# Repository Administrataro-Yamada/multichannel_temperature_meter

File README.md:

# multichannel_temperature_meter

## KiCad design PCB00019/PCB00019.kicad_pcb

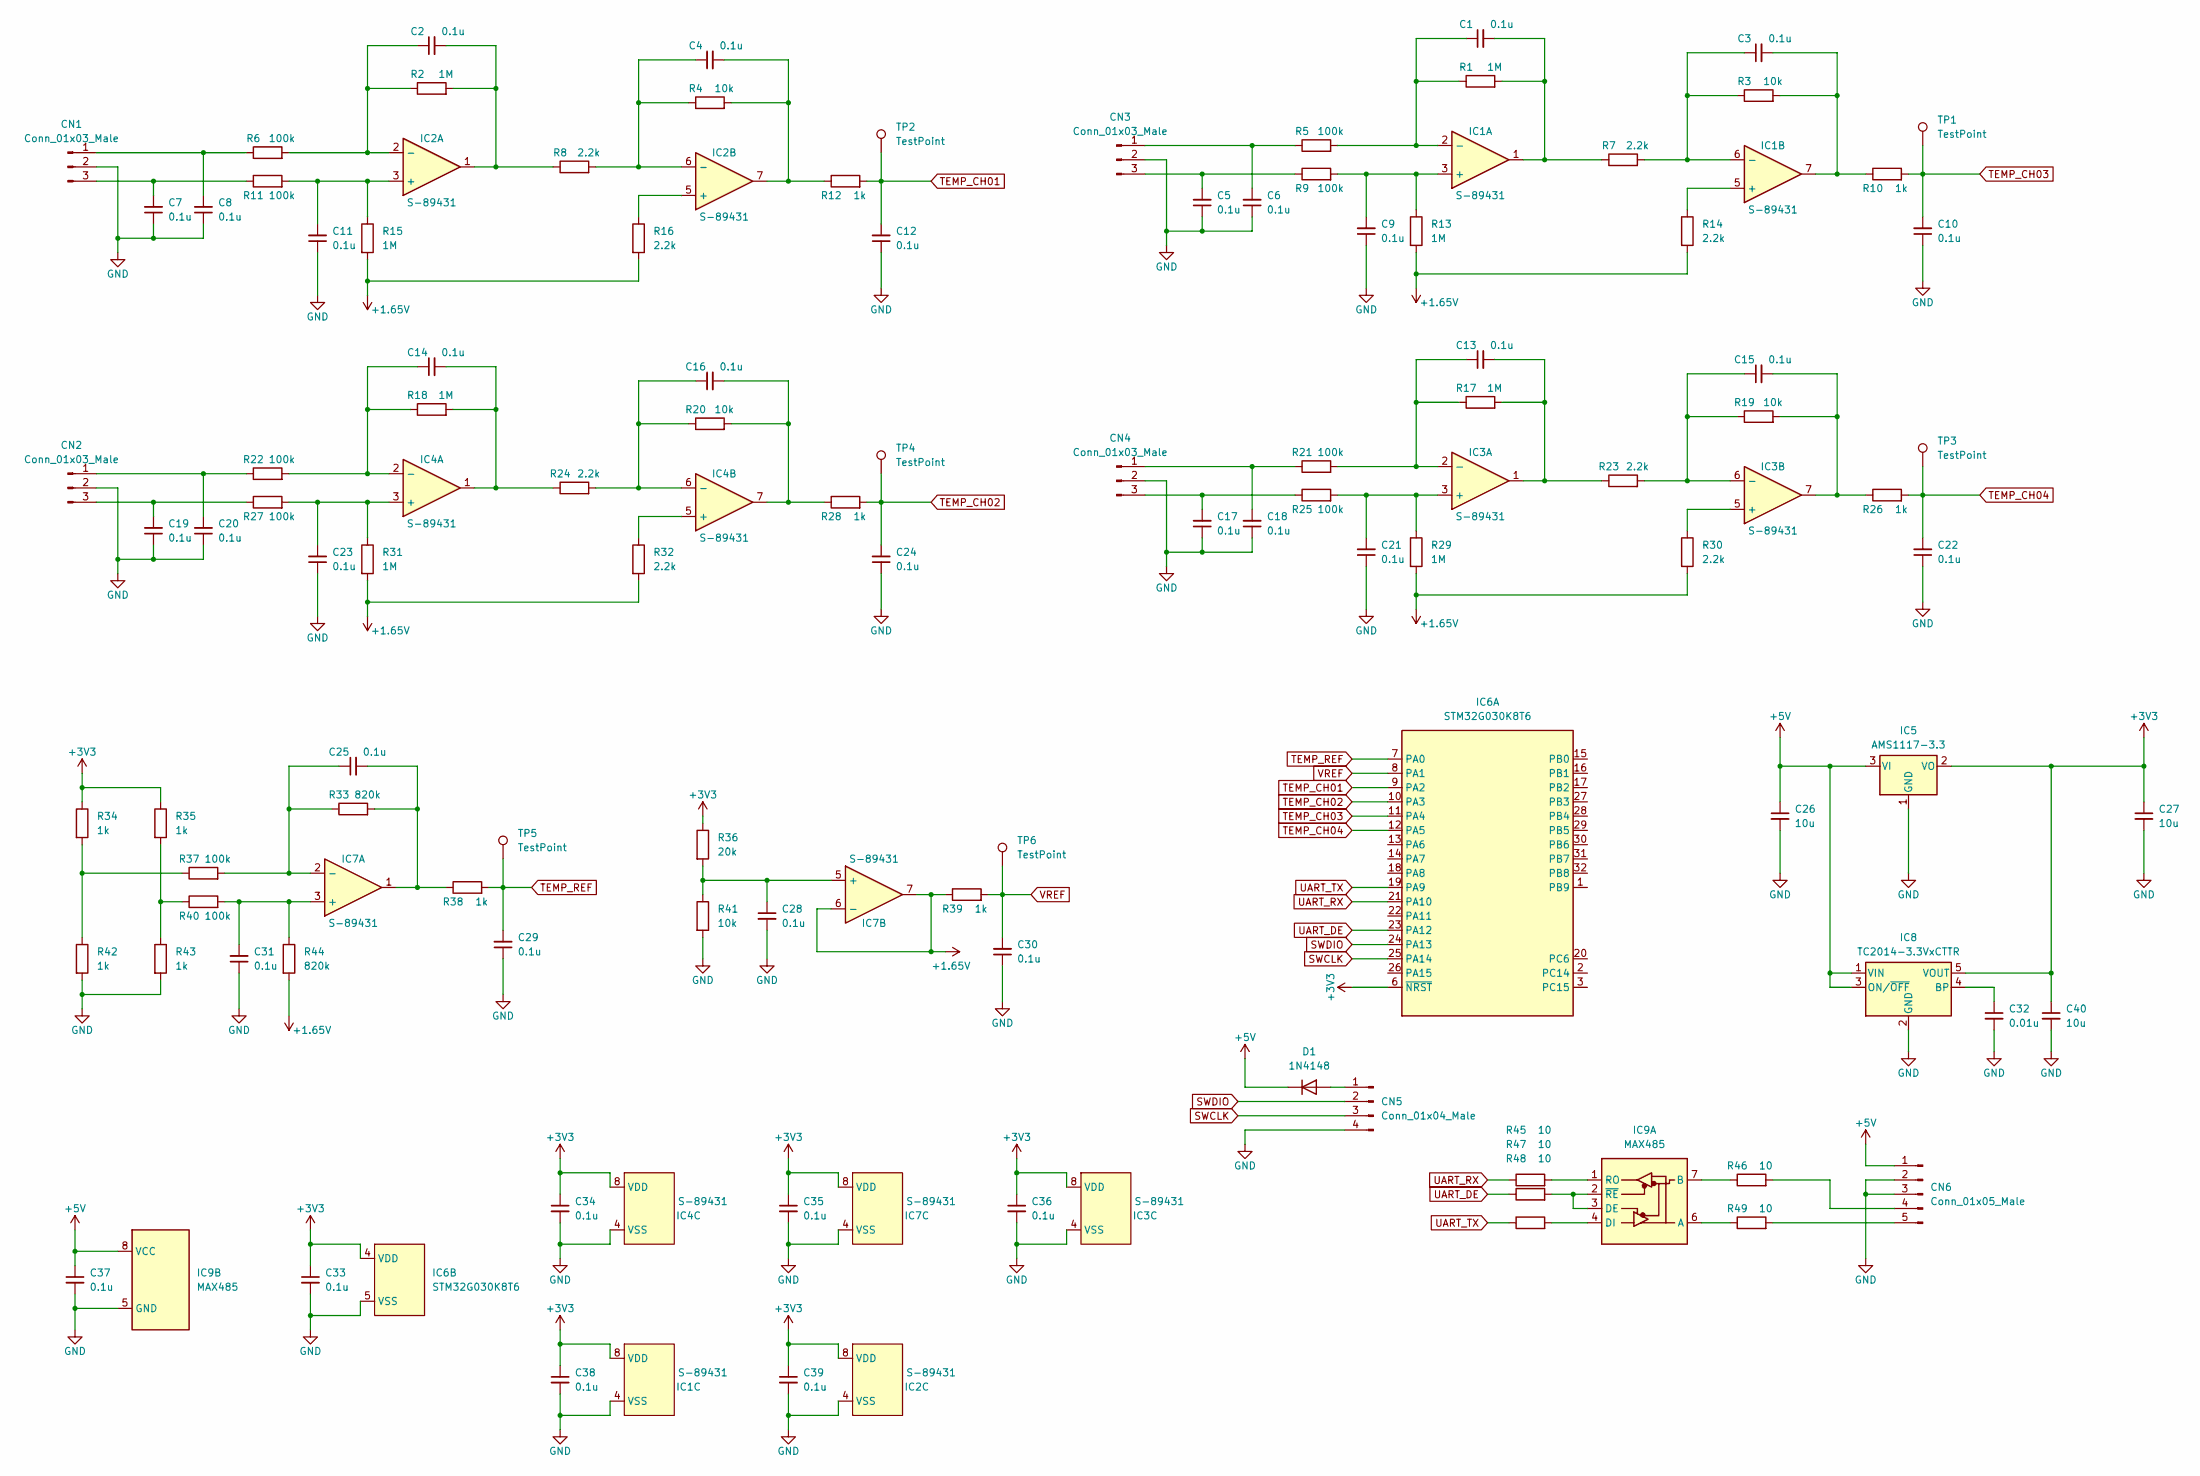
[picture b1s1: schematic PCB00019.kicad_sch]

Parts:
C1, C2, C3, C4, C5, C6, C7, C8, C9, C10, C11, C12, C13, C14, C15, C16, C17, C18, C19, C20, C21, C22, C23, C24, C25, C28, C29, C30, C31, C33, C34, C35, C36, C37, C38, C39: 0.1u; C_0603_1608Metric
C26, C27, C40: 10u; C_0805_2012Metric
C32: 0.01u; C_0805_2012Metric
CN1, CN2, CN3, CN4: Conn_01x03_Male; TerminalBlock_bornier-3_P5.08mm
CN5: Conn_01x04_Male; PinHeader_1x04_P2.54mm_Vertical
CN6: Conn_01x05_Male; TerminalBlock_bornier-5_P5.08mm
D1: 1N4148; D_SOD-123
IC1, IC2, IC3, IC4, IC7: S-89431; MSOP-8_3x3mm_P0.65mm
IC5: AMS1117-3.3; SOT-223-3_TabPin2
IC6: STM32G030K8T6; LQFP-32_7x7mm_P0.8mm
IC8: TC2014-3.3VxCTTR; SOT-23-5
IC9: MAX485; SOIC-8_3.9x4.9mm_P1.27mm
R1, R2, R13, R15, R17, R18, R29, R31: 1M; R_0603_1608Metric
R3, R4, R19, R20, R41: 10k; R_0603_1608Metric
R5, R6, R9, R11, R21, R22, R25, R27, R37, R40: 100k; R_0603_1608Metric
R7, R8, R14, R16, R23, R24, R30, R32: 2.2k; R_0603_1608Metric
R10, R12, R26, R28, R34, R35, R38, R39, R42: 1k; R_0603_1608Metric
R33, R44: 820k; R_0603_1608Metric
R36: 20k; R_0603_1608Metric
R43: 1k; R_Axial_DIN0207_L6.3mm_D2.5mm_P10.16mm_Horizontal
R45, R46, R47, R48, R49: 10; R_0603_1608Metric
TP1, TP2, TP3, TP4, TP5, TP6: TestPoint; TestPoint_Pad_2.0x2.0mm

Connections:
+1V5: IC7.6 (-), IC7.7, R13.2, R14.2, R15.2, R16.2, R29.2, R30.2, R31.2, R32.2, R39.1, R44.2
+3V3: C27.1, C33.1, C34.1, C35.1, C36.1, C38.1, C39.1, C40.1, IC1.8 (VDD), IC2.8 (VDD), IC3.8 (VDD), IC4.8 (VDD), IC5.2 (VO), IC6.4 (VDD), IC6.6 (~NRST), IC7.8 (VDD), IC8.5 (VOUT), R34.1, R35.1, R36.1
+5V: C26.1, C37.1, CN6.1, D1.1 (K), IC5.3 (VI), IC8.1 (VIN), IC8.3 (ON/~OFF), IC9.8 (VCC)
GND: C5.1, C6.1, C7.1, C8.1, C9.1, C10.1, C11.1, C12.1, C17.1, C18.1, C19.1, C20.1, C21.1, C22.1, C23.1, C24.1, C26.2, C27.2, C28.2, C29.1, C30.1, C31.1, C32.2, C33.2, C34.2, C35.2, C36.2, C37.2, C38.2, C39.2, C40.2, CN1.2, CN2.2, CN3.2, CN4.2, CN5.4, CN6.2, CN6.3, IC1.4 (VSS), IC2.4 (VSS), IC3.4 (VSS), IC4.4 (VSS), IC5.1 (GND), IC6.5 (VSS), IC7.4 (VSS), IC8.2 (GND), IC9.5 (GND), R41.2, R42.2, R43.2
unnamed: C1.1, IC1.2 (-), R1.1, R5.2
unnamed: C1.2, IC1.1, R1.2, R7.1
unnamed: C2.1, IC2.2 (-), R2.1, R6.2
unnamed: C2.2, IC2.1, R2.2, R8.1
unnamed: C3.1, IC1.6 (-), R3.1, R7.2
unnamed: C3.2, IC1.7, R3.2, R10.1
unnamed: C4.1, IC2.6 (-), R4.1, R8.2
unnamed: C4.2, IC2.7, R4.2, R12.1
unnamed: C5.2, CN3.3, R9.1
unnamed: C6.2, CN3.1, R5.1
unnamed: C7.2, CN1.3, R11.1
unnamed: C8.2, CN1.1, R6.1
unnamed: C9.2, IC1.3 (+), R9.2, R13.1
unnamed: C11.2, IC2.3 (+), R11.2, R15.1
unnamed: C13.1, IC3.2 (-), R17.1, R21.2
unnamed: C13.2, IC3.1, R17.2, R23.1
unnamed: C14.1, IC4.2 (-), R18.1, R22.2
unnamed: C14.2, IC4.1, R18.2, R24.1
unnamed: C15.1, IC3.6 (-), R19.1, R23.2
unnamed: C15.2, IC3.7, R19.2, R26.1
unnamed: C16.1, IC4.6 (-), R20.1, R24.2
unnamed: C16.2, IC4.7, R20.2, R28.1
unnamed: C17.2, CN4.3, R25.1
unnamed: C18.2, CN4.1, R21.1
unnamed: C19.2, CN2.3, R27.1
unnamed: C20.2, CN2.1, R22.1
unnamed: C21.2, IC3.3 (+), R25.2, R29.1
unnamed: C23.2, IC4.3 (+), R27.2, R31.1
unnamed: C25.1, IC7.2 (-), R33.1, R37.2
unnamed: C25.2, IC7.1, R33.2, R38.1
unnamed: C28.1, IC7.5 (+), R36.2, R41.1
unnamed: C31.2, IC7.3 (+), R40.2, R44.1
unnamed: C32.1, IC8.4 (BP)
unnamed: CN6.4, R46.2
unnamed: CN6.5, R49.2
unnamed: CN5.1, D1.2 (A)
unnamed: IC1.5 (+), R14.1
unnamed: IC2.5 (+), R16.1
unnamed: IC3.5 (+), R30.1
unnamed: IC4.5 (+), R32.1
unnamed: IC9.1 (RO), R45.2
unnamed: IC9.2 (~RE), IC9.3 (DE), R47.2
unnamed: IC9.4 (DI), R48.2
unnamed: IC9.6 (A), R49.1
unnamed: IC9.7 (B), R46.1
unnamed: R34.2, R37.1, R42.1
unnamed: R35.2, R40.1, R43.1
SWCLK: CN5.3, IC6.25 (PA14)
SWDIO: CN5.2, IC6.24 (PA13)
TEMP_CH01: C12.2, IC6.9 (PA2), R12.2, TP2.1
TEMP_CH02: C24.2, IC6.10 (PA3), R28.2, TP4.1
TEMP_CH03: C10.2, IC6.11 (PA4), R10.2, TP1.1
TEMP_CH04: C22.2, IC6.12 (PA5), R26.2, TP3.1
TEMP_REF: C29.2, IC6.7 (PA0), R38.2, TP5.1
UART_DE: IC6.23 (PA12), R47.1
UART_RX: IC6.21 (PA10), R45.1
UART_TX: IC6.19 (PA9), R48.1
VREF: C30.2, IC6.8 (PA1), R39.2, TP6.1

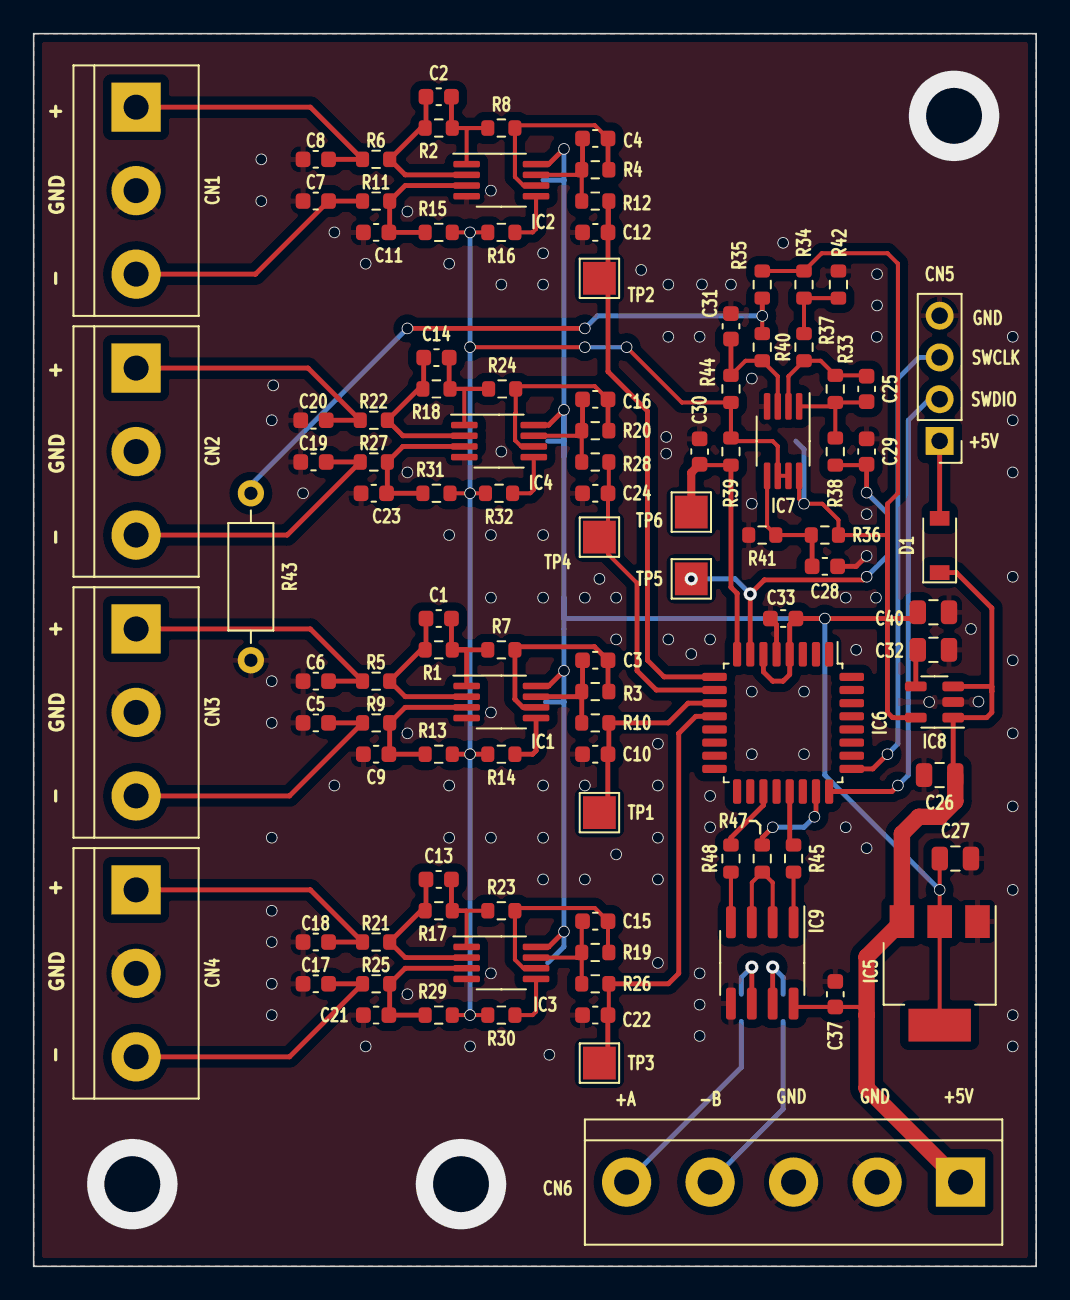
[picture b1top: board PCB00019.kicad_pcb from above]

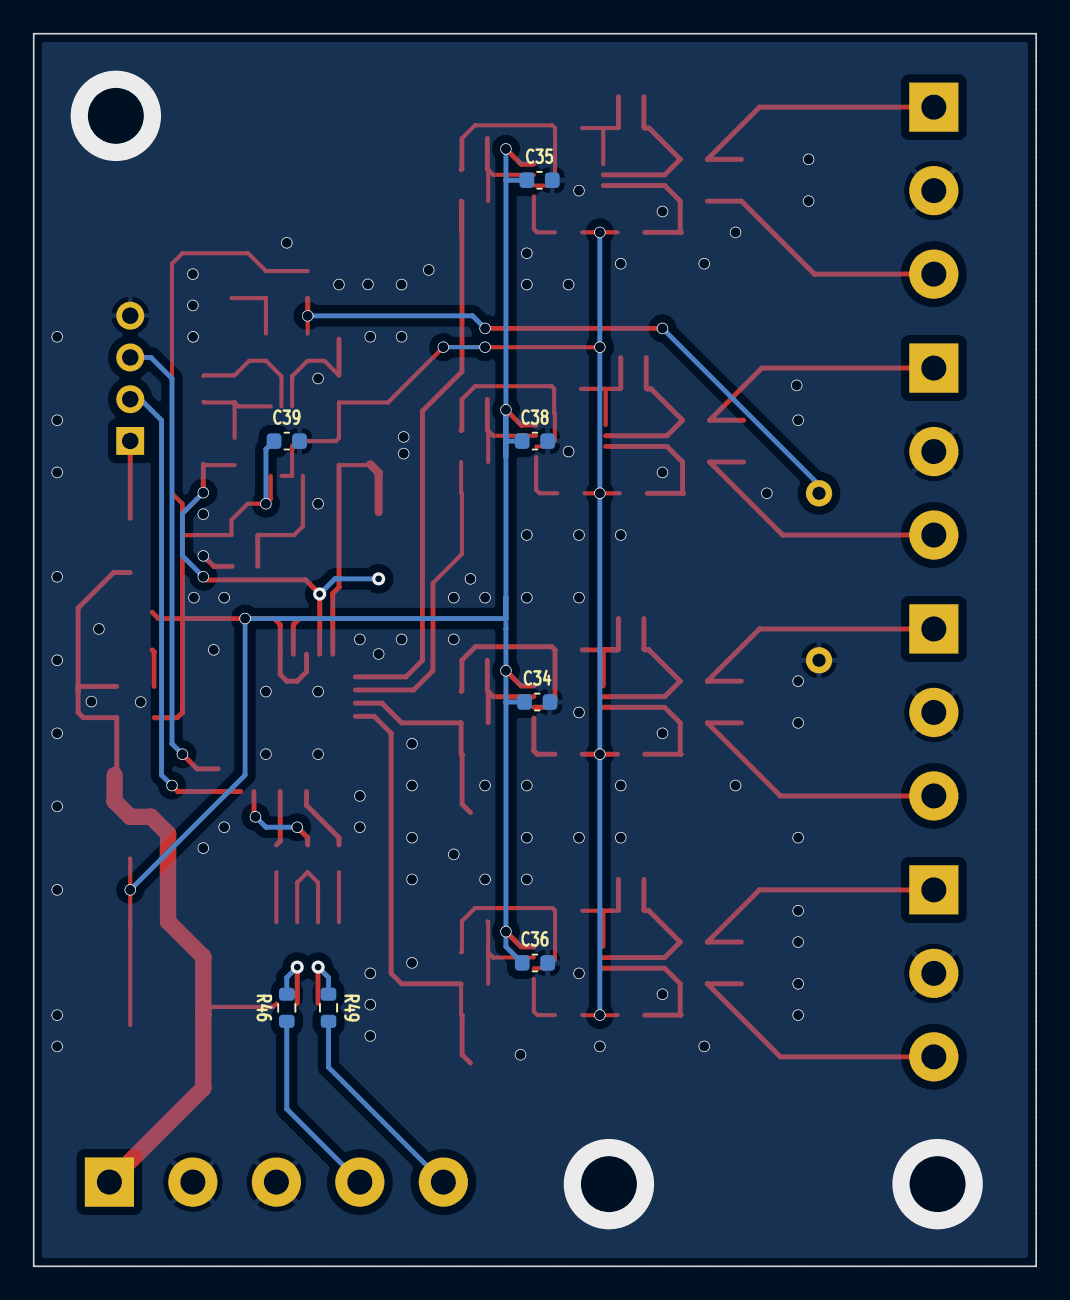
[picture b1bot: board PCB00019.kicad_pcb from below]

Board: 2 copper layers, 61.0 x 75.0 mm, 111 parts (7 on the bottom side), 62 nets.

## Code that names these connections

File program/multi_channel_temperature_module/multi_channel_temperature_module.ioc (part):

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Mcu.Name=STM32G030K(6-8)Tx
Mcu.Package=LQFP32
Mcu.UserName=STM32G030K8Tx
PA0.Mode=IN0
PA0.Signal=ADC1_IN0
PA1.Mode=IN1
PA1.Signal=ADC1_IN1
PA10.Mode=Asynchronous
PA10.Signal=USART1_RX
PA12\ [PA10].Mode=Hardware Flow Control (RS485)
PA12\ [PA10].Signal=USART1_DE
PA13.Mode=Serial_Wire
PA13.Signal=SYS_SWDIO
PA14-BOOT0.Mode=Serial_Wire
PA14-BOOT0.Signal=SYS_SWCLK
PA2.Mode=IN2
PA2.Signal=ADC1_IN2
PA3.Mode=IN3
PA3.Signal=ADC1_IN3
PA4.Mode=IN4
PA4.Signal=ADC1_IN4
PA5.Mode=IN5
PA5.Signal=ADC1_IN5
PA9.Mode=Asynchronous
PA9.Signal=USART1_TX
RCC.HSE_VALUE=8000000
RCC.SYSCLKFreq_VALUE=64000000
RCC.SYSCLKSource=RCC_SYSCLKSOURCE_PLLCLK
board=custom

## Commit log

2023-09-14 no message
